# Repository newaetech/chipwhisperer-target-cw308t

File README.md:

# ChipWhisperer CW308 Targets #

These are *targets* for the CW308 UFO Board. This repo contains gerbers, schematics, and source files (in Altium Designer format). Note **SOME BOARDS ARE UNTESTED**. All files are provided at your own risk. The CW308 UFO board is required for use (not part of this repo) as it supplies power, clock, programming headers etc:

Many of these target boards (along with UFO baseboard) can be purchased assembled via Mouser Electronics. Note all targets are available however, so if you want some of the latest targets you may need to build one.

Most (all?) of these boards support the ChipWhisperer example applications. That means a basic HAL is provided in [chipwhisperer/firmware/mcu/hal](https://github.com/newaetech/chipwhisperer/tree/develop/firmware/mcu/hal) . Some of the more unique boards do not build as part of that system due to complexity of porting (i.e., ESP32).

## Documentation ##

The documentation in each directory (the markdown README.md file) is mirrored to the ChipWhisperer [main documentation page](https://chipwhisperer.readthedocs.io).
Some of the links in the markdown files here appear broken; they are written to
work for building the documentation site at
https://github.com/newaetech/chipwhisperer/tree/develop/docs, where this
repository is pulled in as a submodule.

## Using Boards ##

To use the boards, you will require the following at minimum:

* CW308 UFO Baseboard
* Analysis/injection device: either (1) ChipWhisperer-Lite Capture or ChipWhisperer-Pro, or (2) oscilloscope.

If NOT using ChipWhisperer-Lite/Pro which have built-in power supply, serial comms, and clock generator:

* USB-Serial adapter (3.3V)
* Crystal on UFO board (included w/ UFO board)
* 2.1mm DC power jack and 5V power supply

For most boards you will also require:
* External programming tool.

The STM32Fx boards, XMEGA, and AVR boards can all be programmed from the ChipWhisperer platform. All other boards will require an external programmer at this time.

### Suggested programmers ###

* For ARM targets anything with 20-pin JTAG header such as J-Link, OpenOCD, etc.
* For PowerPC targets a PEMicro USB Multilink
* For Tri-Core targets DAP miniWiggler V3
* For ESP32 you only need a USB-Serial cable
* Others (Si4010, D2000, etc) may have unique requirements.

## FAQs ##

**Q**: Do these boards work stand-alone?

**A**: No. These boards require a CW308 UFO Base-Board. In addition you may need an external programmer to load code on many of them.

--

**Q**: What's the difference between these and dev-boards?

**A**: These boards are purpose-built for side-channel analysis. As such they have a shunt resistor mounted, along with missing decoupling capacitors to allow clean power measurements. You can hack up dev-boards to achieve this, but these CW308T boards make it considerably easier to do so, along with high repeatability.

--

**Q:** Why are these boards so expensive when there is nothing on it? I can buy a dev-kit with JTAG and everything for the cost of some of these boards!

**A:** Dev-boards have low cost as are produced in huge quantity and minimal profit margin. Due to the unique nature of our boards we typically are producing QTY 25-200 per "run", and many of the ICs alone are rather expensive at that point. For example a STM32F407 @ Qty 40 is $12 USD, and the "discovery" board with that chip mounted is only $20!

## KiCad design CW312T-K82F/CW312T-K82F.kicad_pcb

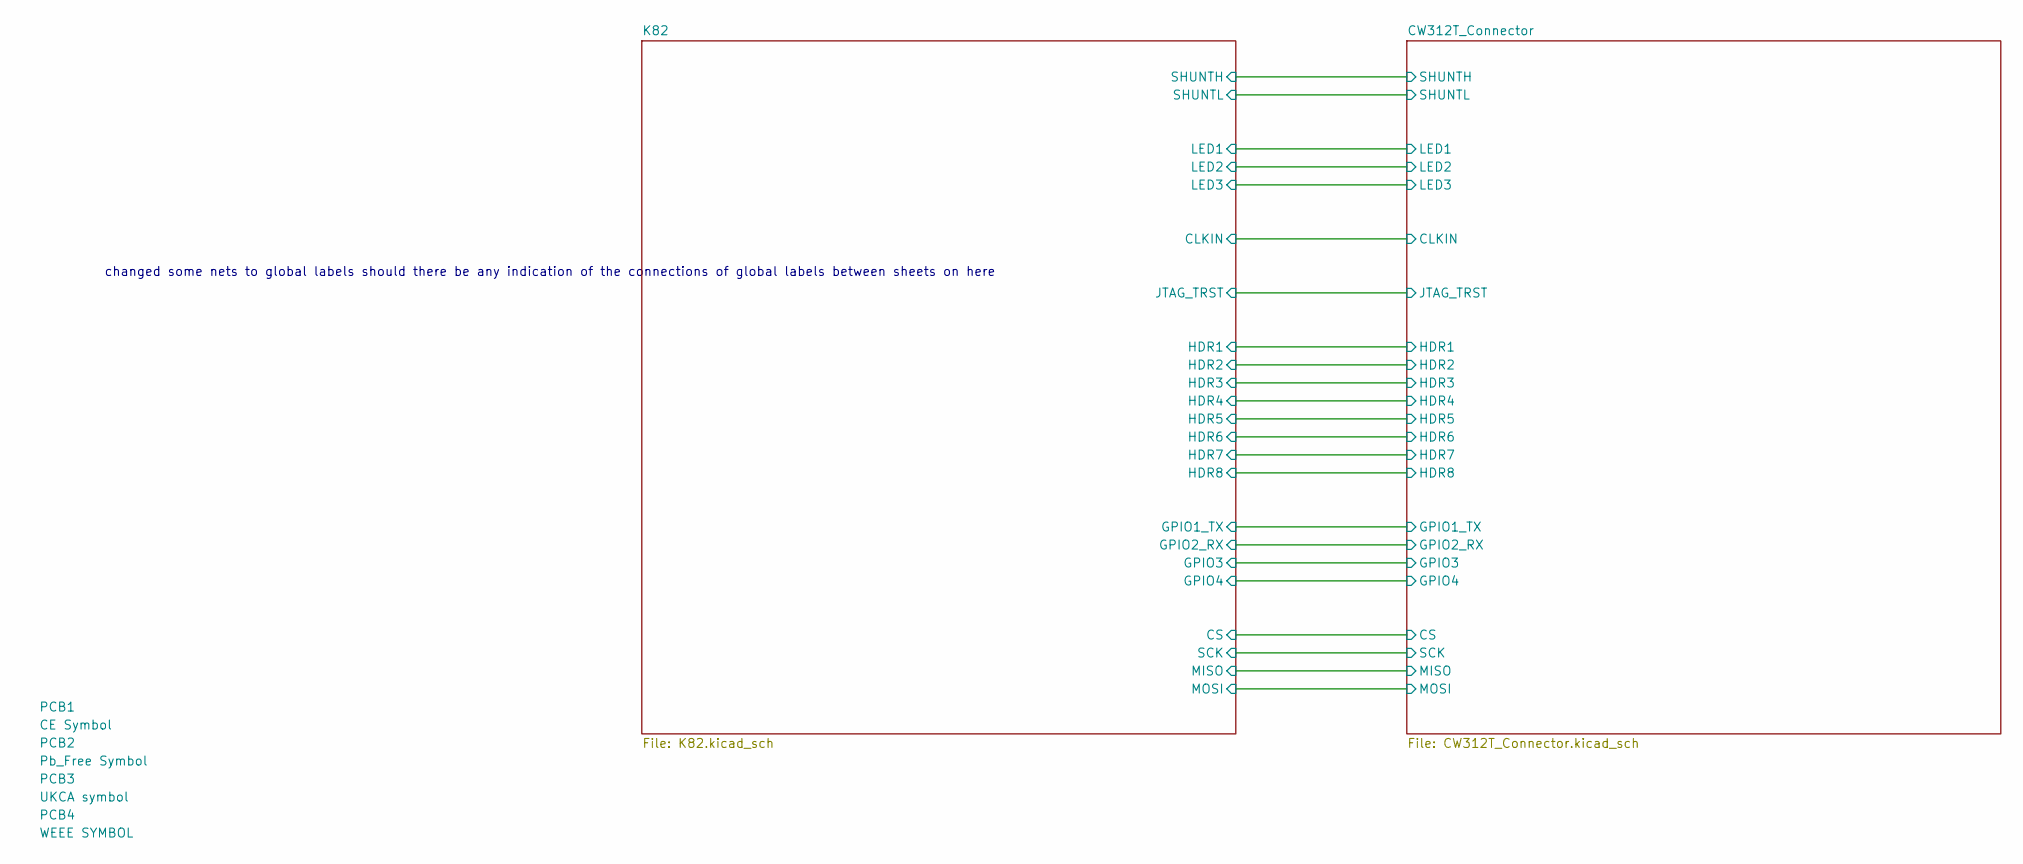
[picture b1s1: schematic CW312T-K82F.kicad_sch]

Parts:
PCB1: CE Symbol; CE-Logo_8.5x6mm_SilkScreen
PCB2: Pb_Free Symbol; Pb_Free_8.0x8.0mm_SilkScreen
PCB3: UKCA symbol; UKCA-Logo_8x8mm_SilkScreen
PCB4: WEEE SYMBOL; WEEE-Logo_5.6x8mm_SilkScreen

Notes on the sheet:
changed some nets to global labels should there be any indication of the connections of global labels between sheets on here

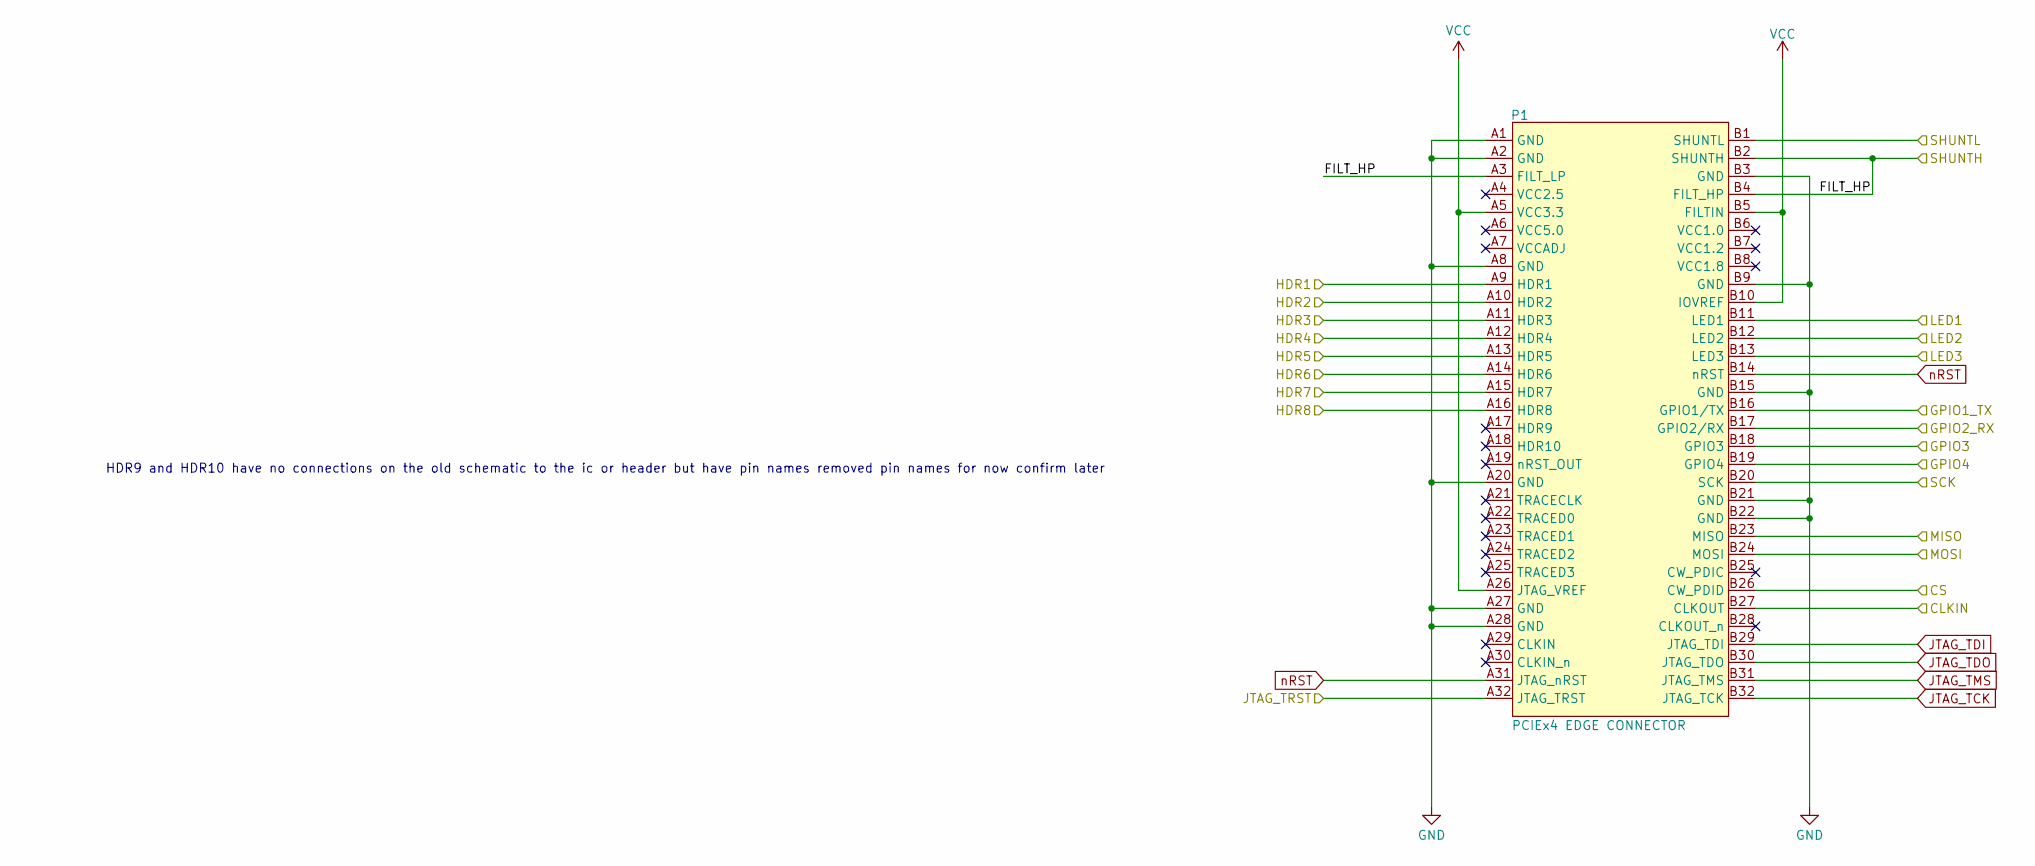
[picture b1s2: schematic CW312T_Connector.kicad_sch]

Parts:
P1: PCIEx4 EDGE CONNECTOR; CW312_Template

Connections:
/CW312T_Connector/CLKIN: P1.B27 (CLKOUT); also elsewhere on the board
/CW312T_Connector/CS: P1.B26 (CW_PDID); also elsewhere on the board
/CW312T_Connector/FILT_HP: P1.A3 (FILT_LP), P1.B2 (SHUNTH), P1.B4 (FILT_HP); also elsewhere on the board
/CW312T_Connector/GPIO1_TX: P1.B16 (GPIO1/TX); also elsewhere on the board
/CW312T_Connector/GPIO2_RX: P1.B17 (GPIO2/RX); also elsewhere on the board
/CW312T_Connector/GPIO3: P1.B18 (GPIO3); also elsewhere on the board
/CW312T_Connector/GPIO4: P1.B19 (GPIO4); also elsewhere on the board
/CW312T_Connector/HDR1: P1.A9 (HDR1); also elsewhere on the board
/CW312T_Connector/HDR2: P1.A10 (HDR2); also elsewhere on the board
/CW312T_Connector/HDR3: P1.A11 (HDR3); also elsewhere on the board
/CW312T_Connector/HDR4: P1.A12 (HDR4); also elsewhere on the board
/CW312T_Connector/HDR5: P1.A13 (HDR5); also elsewhere on the board
/CW312T_Connector/HDR6: P1.A14 (HDR6); also elsewhere on the board
/CW312T_Connector/HDR7: P1.A15 (HDR7); also elsewhere on the board
/CW312T_Connector/HDR8: P1.A16 (HDR8); also elsewhere on the board
/CW312T_Connector/JTAG_TRST: P1.A32 (JTAG_TRST); also elsewhere on the board
/CW312T_Connector/LED1: P1.B11 (LED1); also elsewhere on the board
/CW312T_Connector/LED2: P1.B12 (LED2); also elsewhere on the board
/CW312T_Connector/LED3: P1.B13 (LED3); also elsewhere on the board
/CW312T_Connector/MISO: P1.B23 (MISO); also elsewhere on the board
/CW312T_Connector/MOSI: P1.B24 (MOSI); also elsewhere on the board
/CW312T_Connector/SCK: P1.B20 (SCK); also elsewhere on the board
/CW312T_Connector/SHUNTL: P1.B1 (SHUNTL); also elsewhere on the board
GND: P1.A1 (GND), P1.A2 (GND), P1.A8 (GND), P1.A20 (GND), P1.A27 (GND), P1.A28 (GND), P1.B3 (GND), P1.B9 (GND), P1.B15 (GND), P1.B21 (GND), P1.B22 (GND); also elsewhere on the board
JTAG_TCK: P1.B32 (JTAG_TCK); also elsewhere on the board
JTAG_TDI: P1.B29 (JTAG_TDI); also elsewhere on the board
JTAG_TDO: P1.B30 (JTAG_TDO); also elsewhere on the board
JTAG_TMS: P1.B31 (JTAG_TMS); also elsewhere on the board
VCC: P1.A5 (VCC3.3), P1.A26 (JTAG_VREF), P1.B5 (FILTIN), P1.B10 (IOVREF); also elsewhere on the board
nRST: P1.A31 (JTAG_nRST), P1.B14 (nRST); also elsewhere on the board

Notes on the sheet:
HDR9 and HDR10 have no connections on the old schematic to the ic or header but have pin names removed pin names for now confirm later

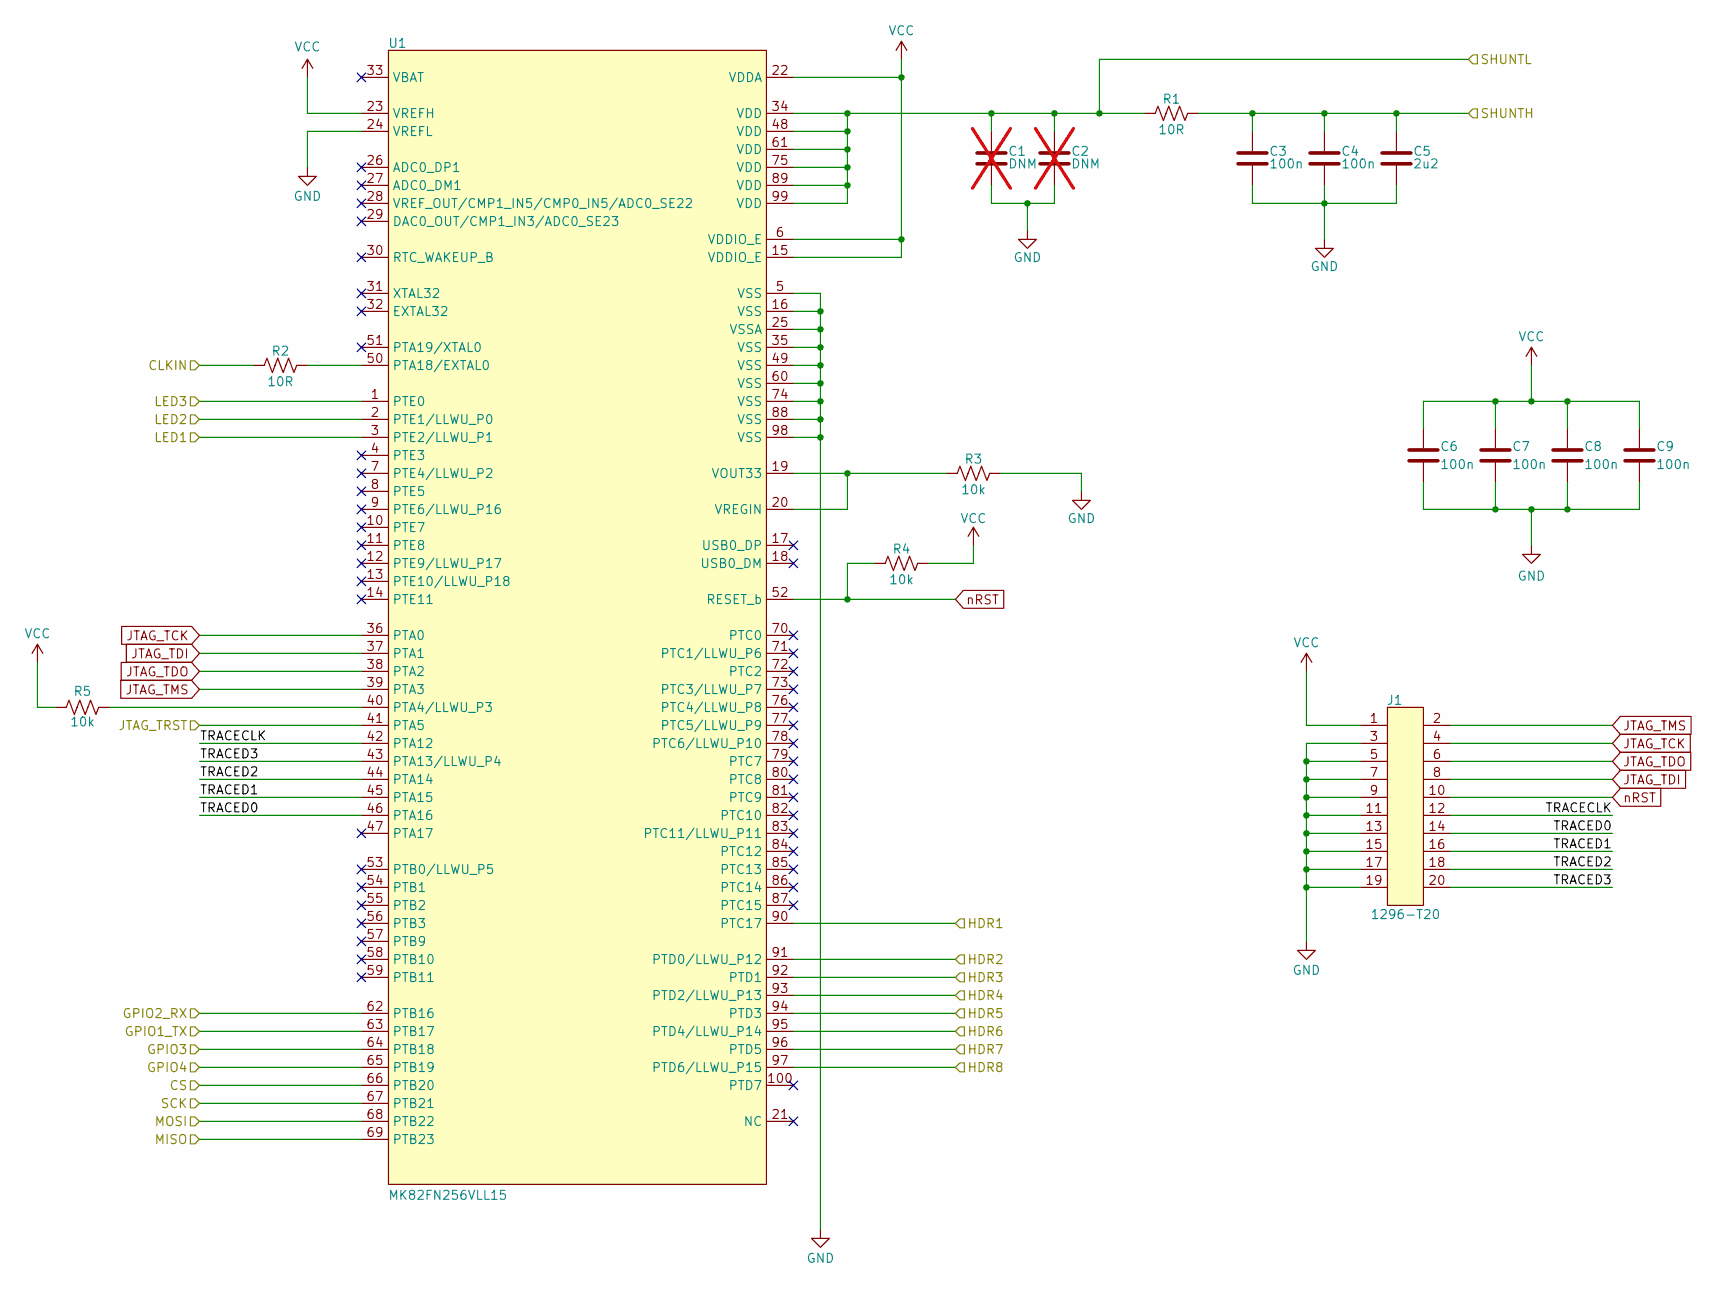
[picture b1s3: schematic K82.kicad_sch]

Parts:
C1, C2: DNM_CAP_0603; C_0603_1608Metric; Manufacturer Part Number C0603C225K4PAC7867; not fitted
C3, C4, C6, C7, C8, C9: CAP_100n_6.3V_0603; C_0603_1608Metric; Manufacturer Part Number CC0603KRX7R5BB104
C5: CAP_2u2_6.3V_0603; C_0603_1608Metric; Manufacturer Part Number CC0603KRX7R5BB225
J1: 20_pin; PinHeader_2x10_P1.27mm_Vertical_SMD; Manufacturer Part Number 20021121-00020T4LF
R1, R2: RES_10R_0603; R_0603_1608Metric; Manufacturer Part Number RC0603FR-0710RL
R3, R4, R5: RES_10k_0603; R_0603_1608Metric; Manufacturer Part Number RC0603FR-0710KL
U1: MK82FN256VLL15; LQFP-100_14x14mm_P0.5mm; Manufacturer Part Number MK82FN256VLL15

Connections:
/CW312T_Connector/CLKIN: R2.1; also elsewhere on the board
/CW312T_Connector/CS: U1.66 (PTB20); also elsewhere on the board
/CW312T_Connector/FILT_HP: C3.2, C4.2, C5.2, R1.2; also elsewhere on the board
/CW312T_Connector/GPIO1_TX: U1.63 (PTB17); also elsewhere on the board
/CW312T_Connector/GPIO2_RX: U1.62 (PTB16); also elsewhere on the board
/CW312T_Connector/GPIO3: U1.64 (PTB18); also elsewhere on the board
/CW312T_Connector/GPIO4: U1.65 (PTB19); also elsewhere on the board
/CW312T_Connector/HDR1: U1.90 (PTC17); also elsewhere on the board
/CW312T_Connector/HDR2: U1.91 (PTD0/LLWU_P12); also elsewhere on the board
/CW312T_Connector/HDR3: U1.92 (PTD1); also elsewhere on the board
/CW312T_Connector/HDR4: U1.93 (PTD2/LLWU_P13); also elsewhere on the board
/CW312T_Connector/HDR5: U1.94 (PTD3); also elsewhere on the board
/CW312T_Connector/HDR6: U1.95 (PTD4/LLWU_P14); also elsewhere on the board
/CW312T_Connector/HDR7: U1.96 (PTD5); also elsewhere on the board
/CW312T_Connector/HDR8: U1.97 (PTD6/LLWU_P15); also elsewhere on the board
/CW312T_Connector/JTAG_TRST: U1.41 (PTA5); also elsewhere on the board
/CW312T_Connector/LED1: U1.3 (PTE2/LLWU_P1); also elsewhere on the board
/CW312T_Connector/LED2: U1.2 (PTE1/LLWU_P0); also elsewhere on the board
/CW312T_Connector/LED3: U1.1 (PTE0); also elsewhere on the board
/CW312T_Connector/MISO: U1.69 (PTB23); also elsewhere on the board
/CW312T_Connector/MOSI: U1.68 (PTB22); also elsewhere on the board
/CW312T_Connector/SCK: U1.67 (PTB21); also elsewhere on the board
/CW312T_Connector/SHUNTL: C1.2, C2.2, R1.1, U1.34 (VDD), U1.48 (VDD), U1.61 (VDD), U1.75 (VDD), U1.89 (VDD), U1.99 (VDD); also elsewhere on the board
/K82/TRACECLK: J1.12, U1.42 (PTA12)
/K82/TRACED0: J1.14, U1.46 (PTA16)
/K82/TRACED1: J1.16, U1.45 (PTA15)
/K82/TRACED2: J1.18, U1.44 (PTA14)
/K82/TRACED3: J1.20, U1.43 (PTA13/LLWU_P4)
GND: C1.1, C2.1, C3.1, C4.1, C5.1, C6.1, C7.1, C8.1, C9.1, J1.3, J1.5, J1.7, J1.9, J1.11, J1.13, J1.15, J1.17, J1.19, R3.2, U1.5 (VSS), U1.16 (VSS), U1.24 (VREFL), U1.25 (VSSA), U1.35 (VSS), U1.49 (VSS), U1.60 (VSS), U1.74 (VSS), U1.88 (VSS), U1.98 (VSS); also elsewhere on the board
JTAG_TCK: J1.4, U1.36 (PTA0); also elsewhere on the board
JTAG_TDI: J1.8, U1.37 (PTA1); also elsewhere on the board
JTAG_TDO: J1.6, U1.38 (PTA2); also elsewhere on the board
JTAG_TMS: J1.2, U1.39 (PTA3); also elsewhere on the board
unnamed: R5.2, U1.40 (PTA4/LLWU_P3)
unnamed: R2.2, U1.50 (PTA18/EXTAL0)
unnamed: R3.1, U1.19 (VOUT33), U1.20 (VREGIN)
VCC: C6.2, C7.2, C8.2, C9.2, J1.1, R4.2, R5.1, U1.6 (VDDIO_E), U1.15 (VDDIO_E), U1.22 (VDDA), U1.23 (VREFH); also elsewhere on the board
nRST: J1.10, R4.1, U1.52 (RESET_b); also elsewhere on the board

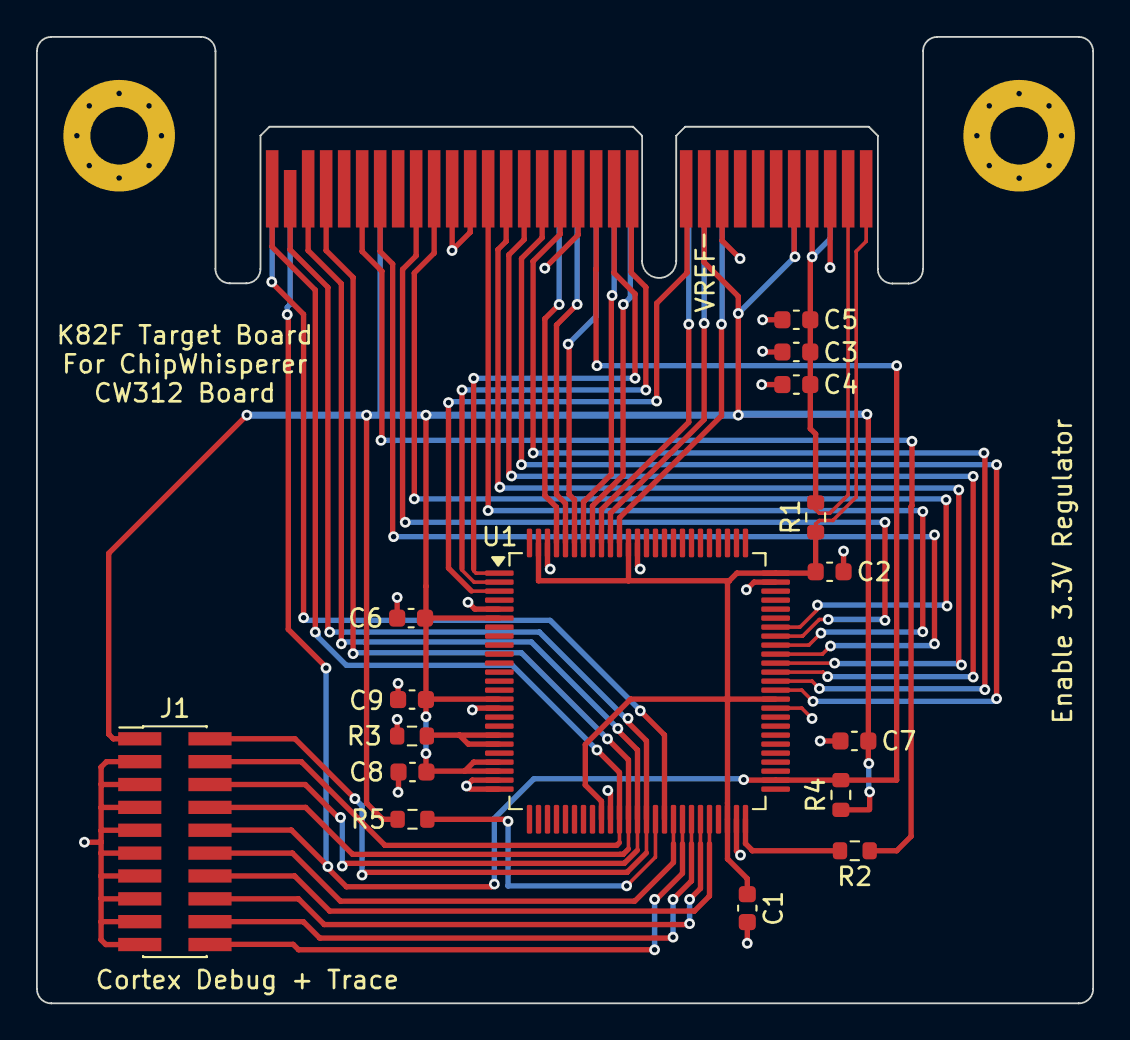
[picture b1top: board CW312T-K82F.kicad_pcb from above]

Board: 2 copper layers, 58.7 x 53.7 mm, 21 parts (0 on the bottom side), 38 nets.

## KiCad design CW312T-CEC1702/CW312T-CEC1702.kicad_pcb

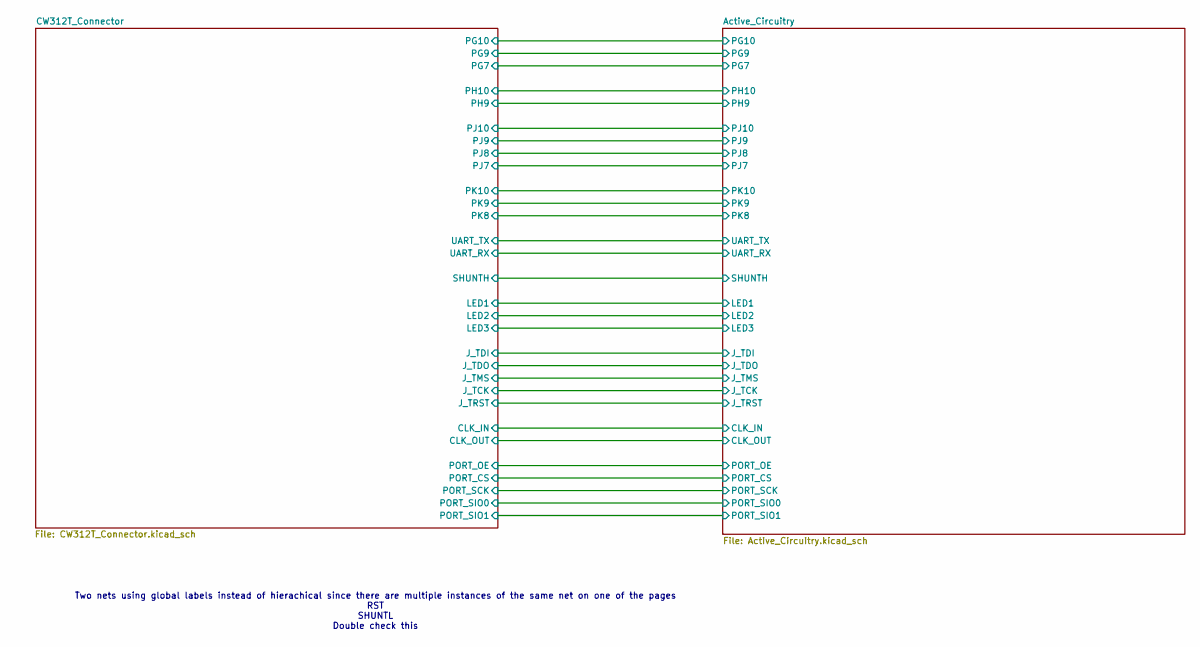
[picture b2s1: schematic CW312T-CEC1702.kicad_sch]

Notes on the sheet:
Two nets using global labels instead of hierachical since there are multiple instances of the same net on one of the pages RST SHUNTL Double check this

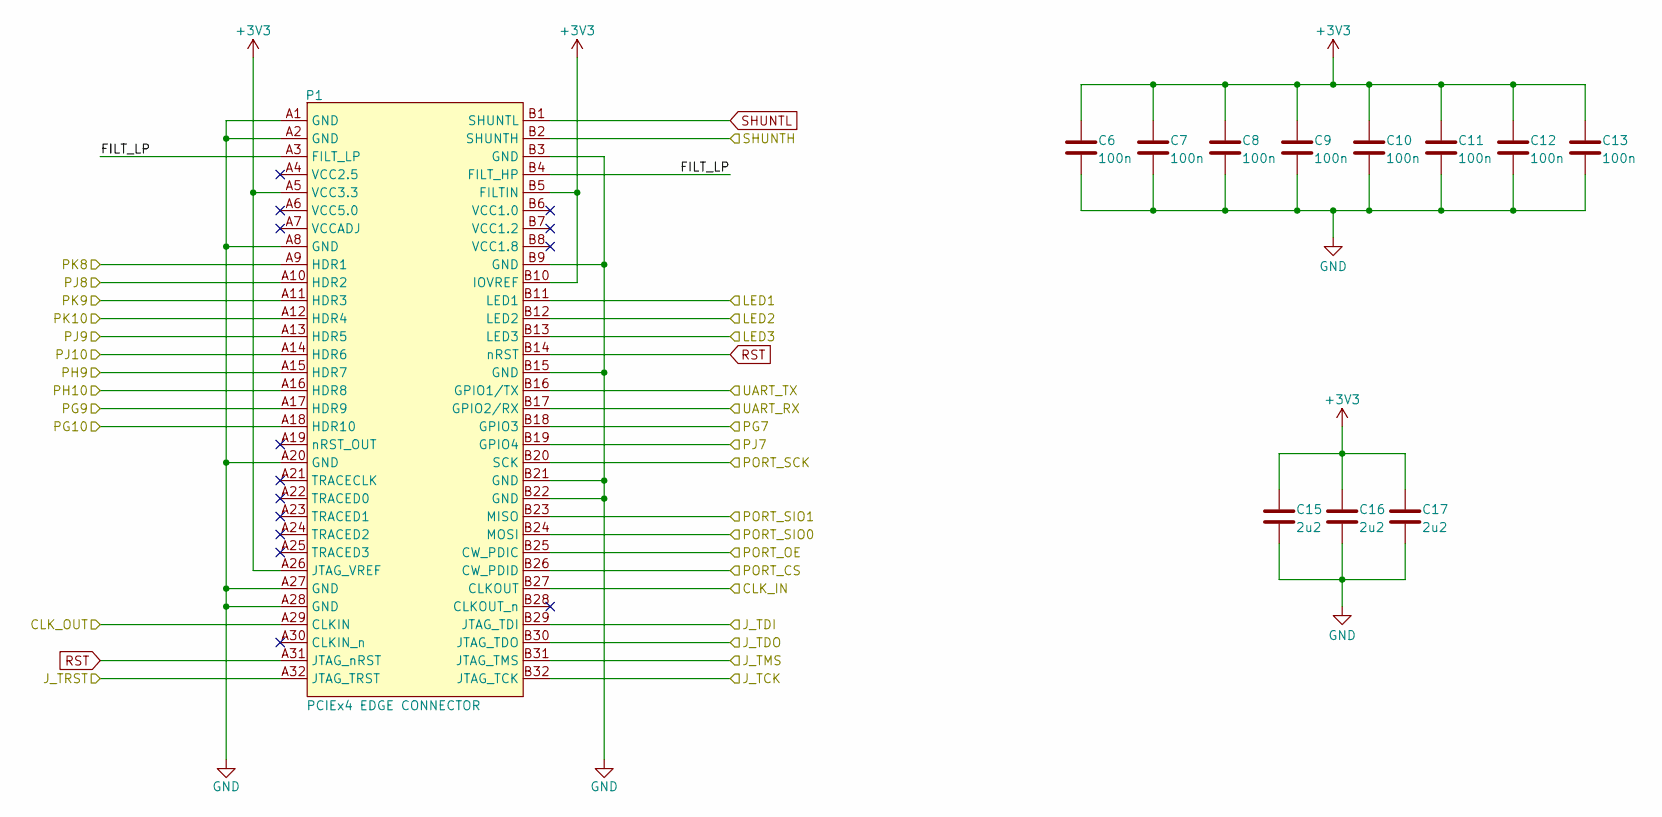
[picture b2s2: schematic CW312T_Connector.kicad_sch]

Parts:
C6, C7, C8, C9, C10, C11, C12, C13: CAP_100n_6.3V_0603; C_0603_1608Metric; Manufacturer Part Number CC0603KRX7R5BB104
C15, C16, C17: CAP_2u2_6.3V_0603; C_0603_1608Metric; Manufacturer Part Number CC0603KRX7R5BB225
P1: PCIEx4 EDGE CONNECTOR; CW312_Template

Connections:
+3V3: C6.2, C7.2, C8.2, C9.2, C10.2, C11.2, C12.2, C13.2, C15.2, C16.2, C17.2, P1.A5 (VCC3.3), P1.A26 (JTAG_VREF), P1.B5 (FILTIN), P1.B10 (IOVREF); also elsewhere on the board
/Active_Circuitry/CLK_IN: P1.B27 (CLKOUT); also elsewhere on the board
/Active_Circuitry/CLK_OUT: P1.A29 (CLKIN); also elsewhere on the board
/Active_Circuitry/J_TCK: P1.B32 (JTAG_TCK); also elsewhere on the board
/Active_Circuitry/J_TDI: P1.B29 (JTAG_TDI); also elsewhere on the board
/Active_Circuitry/J_TDO: P1.B30 (JTAG_TDO); also elsewhere on the board
/Active_Circuitry/J_TMS: P1.B31 (JTAG_TMS); also elsewhere on the board
/Active_Circuitry/J_TRST: P1.A32 (JTAG_TRST); also elsewhere on the board
/Active_Circuitry/LED1: P1.B11 (LED1); also elsewhere on the board
/Active_Circuitry/LED2: P1.B12 (LED2); also elsewhere on the board
/Active_Circuitry/LED3: P1.B13 (LED3); also elsewhere on the board
/Active_Circuitry/PG7: P1.B18 (GPIO3); also elsewhere on the board
/Active_Circuitry/PG9: P1.A17 (HDR9); also elsewhere on the board
/Active_Circuitry/PG10: P1.A18 (HDR10); also elsewhere on the board
/Active_Circuitry/PH9: P1.A15 (HDR7); also elsewhere on the board
/Active_Circuitry/PH10: P1.A16 (HDR8); also elsewhere on the board
/Active_Circuitry/PJ7: P1.B19 (GPIO4); also elsewhere on the board
/Active_Circuitry/PJ8: P1.A10 (HDR2); also elsewhere on the board
/Active_Circuitry/PJ9: P1.A13 (HDR5); also elsewhere on the board
/Active_Circuitry/PJ10: P1.A14 (HDR6); also elsewhere on the board
/Active_Circuitry/PK8: P1.A9 (HDR1); also elsewhere on the board
/Active_Circuitry/PK9: P1.A11 (HDR3); also elsewhere on the board
/Active_Circuitry/PK10: P1.A12 (HDR4); also elsewhere on the board
/Active_Circuitry/PORT_CS: P1.B26 (CW_PDID); also elsewhere on the board
/Active_Circuitry/PORT_OE: P1.B25 (CW_PDIC); also elsewhere on the board
/Active_Circuitry/PORT_SCK: P1.B20 (SCK); also elsewhere on the board
/Active_Circuitry/PORT_SIO0: P1.B24 (MOSI); also elsewhere on the board
/Active_Circuitry/PORT_SIO1: P1.B23 (MISO); also elsewhere on the board
/Active_Circuitry/SHUNTH: P1.B2 (SHUNTH); also elsewhere on the board
/Active_Circuitry/UART_RX: P1.B17 (GPIO2/RX); also elsewhere on the board
/Active_Circuitry/UART_TX: P1.B16 (GPIO1/TX); also elsewhere on the board
/CW312T_Connector/FILT_LP: P1.A3 (FILT_LP), P1.B4 (FILT_HP)
GND: C6.1, C7.1, C8.1, C9.1, C10.1, C11.1, C12.1, C13.1, C15.1, C16.1, C17.1, P1.A1 (GND), P1.A2 (GND), P1.A8 (GND), P1.A20 (GND), P1.A27 (GND), P1.A28 (GND), P1.B3 (GND), P1.B9 (GND), P1.B15 (GND), P1.B21 (GND), P1.B22 (GND); also elsewhere on the board
RST: P1.A31 (JTAG_nRST), P1.B14 (nRST); also elsewhere on the board
SHUNTL: P1.B1 (SHUNTL); also elsewhere on the board

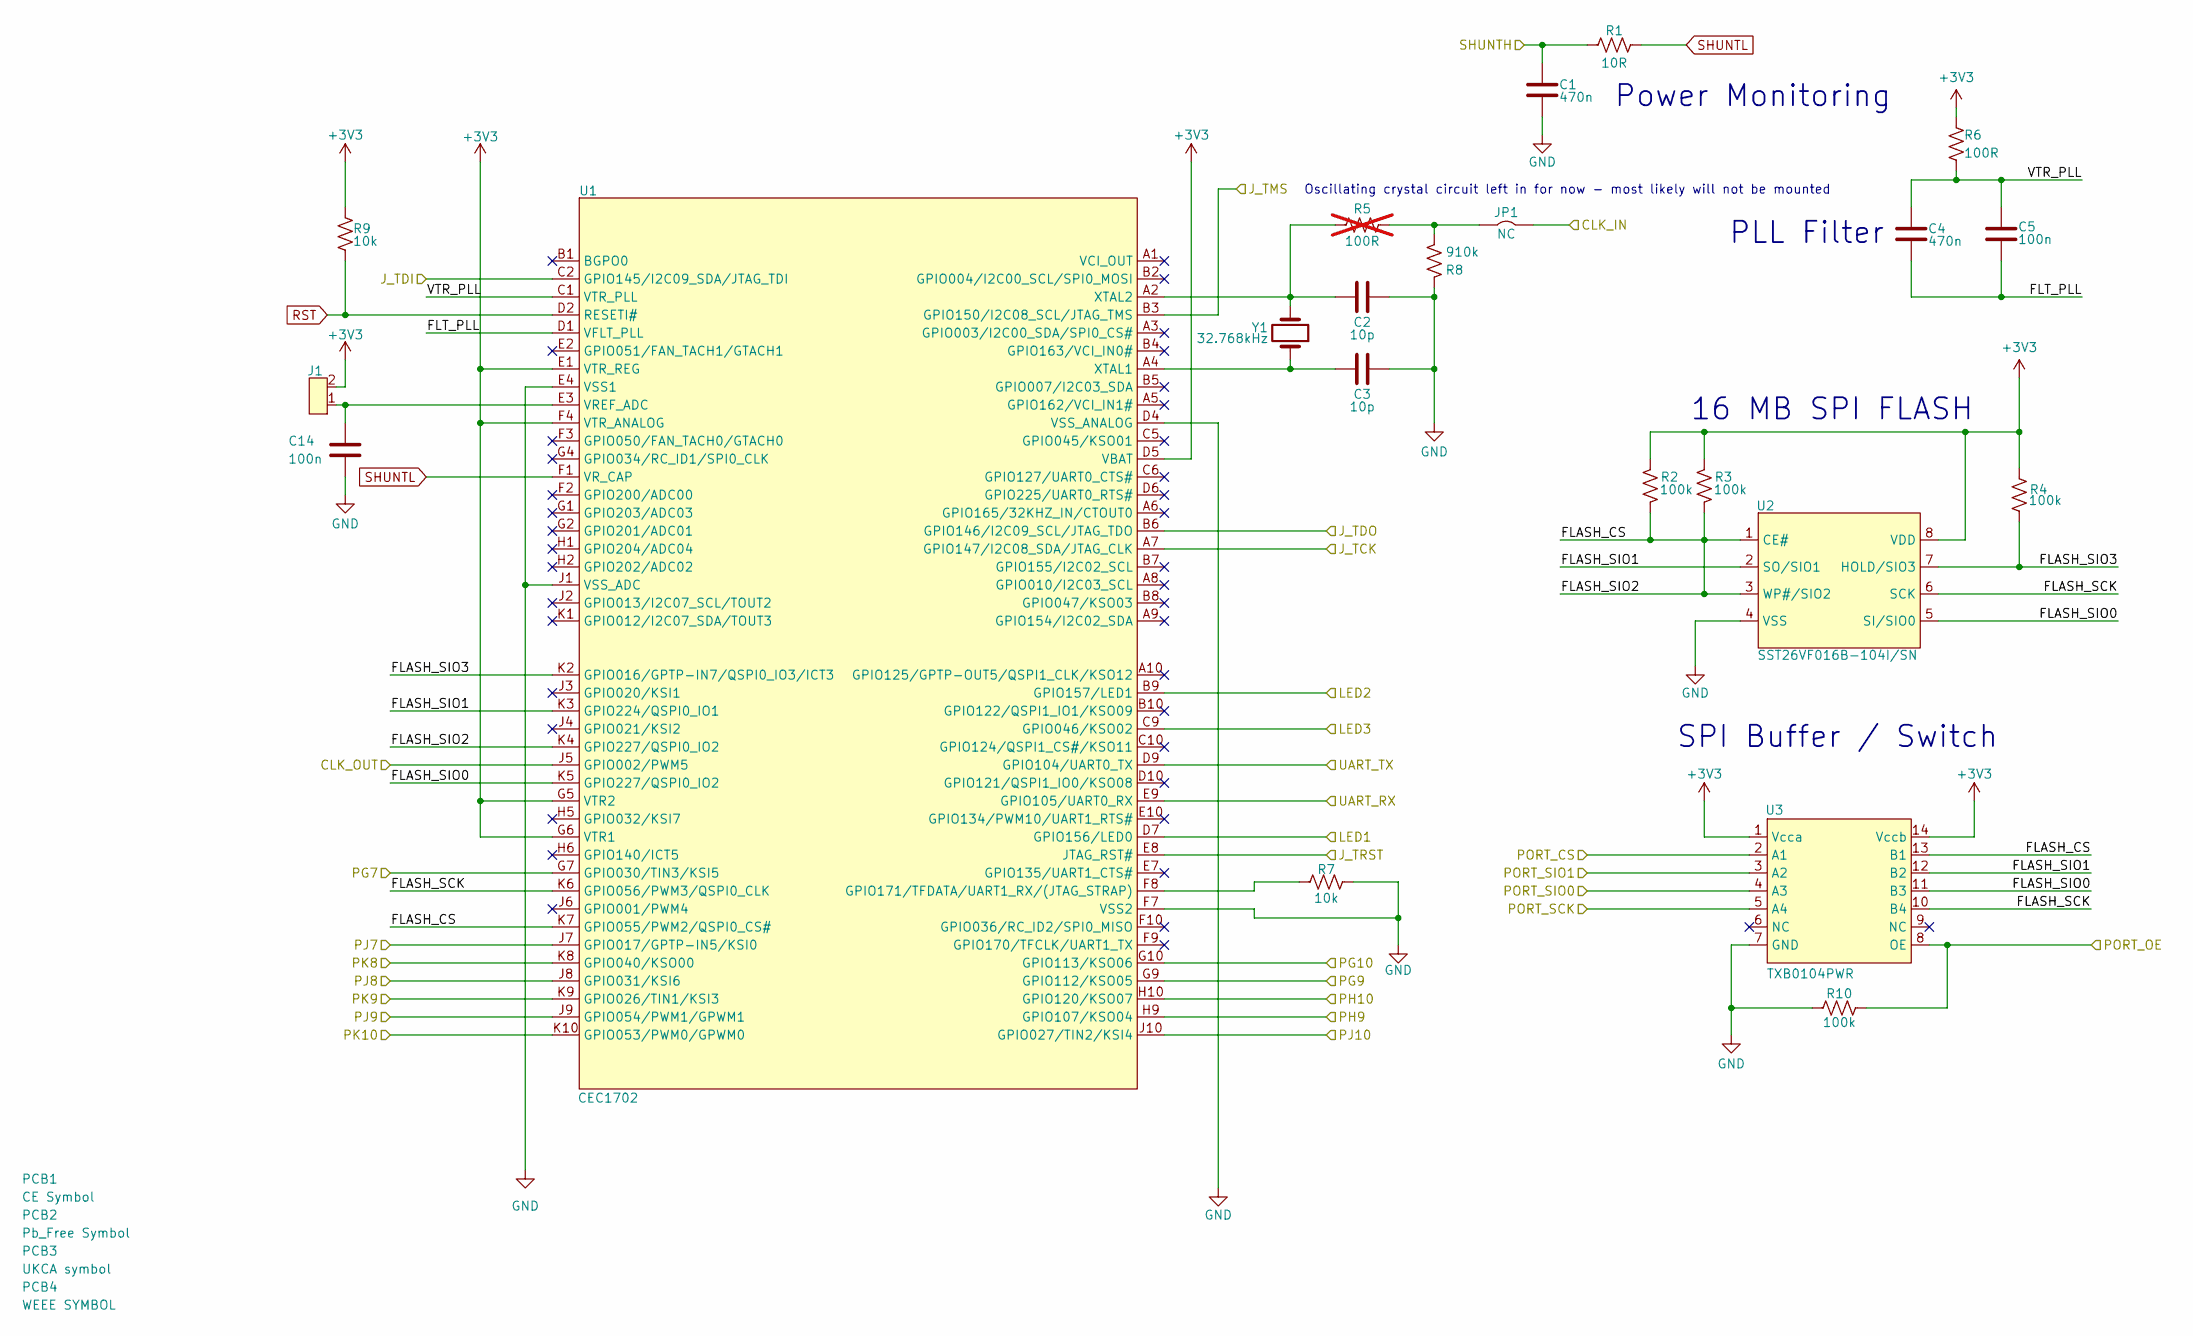
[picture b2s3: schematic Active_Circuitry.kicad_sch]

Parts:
C1, C4: CAP_470n_10V_0603; C_0603_1608Metric; Manufacturer Part Number CC0603KRX7R6BB474
C2, C3: CAP_10p_50V_0603; C_0603_1608Metric; Manufacturer Part Number CC0603JRNPO9BN100
C5: CAP_100n_6.3V_0603; C_0603_1608Metric; Manufacturer Part Number CC0603KRX7R5BB104
C14: CAP_100n_50V_0603; C_0603_1608Metric; Manufacturer Part Number CC0603KRX7R9BB104
J1: 2Pin_Header_2.54; PinHeader_2x01_P2.54mm_Vertical; Manufacturer Part Number M20-9990246
JP1: SolderJumper-2_P1.3mm_Bridged2Bar_Pad1.0x1.5mm
PCB1: CE Symbol; CE-Logo_8.5x6mm_SilkScreen
PCB2: Pb_Free Symbol; Pb_Free_8.0x8.0mm_SilkScreen
PCB3: UKCA symbol; UKCA-Logo_8x8mm_SilkScreen
PCB4: WEEE SYMBOL; WEEE-Logo_5.6x8mm_SilkScreen
R1: RES_10R_0603; R_0603_1608Metric; Manufacturer Part Number RC0603FR-0710RL
R2, R3, R4, R10: RES_100k_0603; R_0603_1608Metric; Manufacturer Part Number RC0603FR-07100KL
R5: RES_100R_0603; R_0603_1608Metric; Manufacturer Part Number RC0603FR-07100RL; not fitted
R6: RES_100R_0603; R_0603_1608Metric; Manufacturer Part Number RC0603FR-07100RL
R7, R9: RES_10k_0603; R_0603_1608Metric; Manufacturer Part Number RC0603FR-0710KL
R8: RES_910k_0603; R_0603_1608Metric; Manufacturer Part Number RC0603FR-07910KL
U1: CEC1702; BGA84C65P10X10_700X700X80; Manufacturer Part Number CEC1702Q-B1-SX-TR
U2: SST26VF016B-104I/SN; SOIC-8_3.9x4.9mm_P1.27mm; Manufacturer Part Number SST26VF016B-104I/SN
U3: TXB0104PWR; SOIC-14_3.9x8.7mm_P1.27mm; Manufacturer Part Number TXB0104PWR
Y1: 32.768kHz; Crystal_SMD_3215-2Pin_3.2x1.5mm; Manufacturer Part Number FC-135 32.7680KA-K0

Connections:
+3V3: J1.2, R2.2, R3.2, R4.1, R6.2, R9.2, U1.D5 (VBAT), U1.E1 (VTR_REG), U1.F4 (VTR_ANALOG), U1.G5 (VTR2), U1.G6 (VTR1), U2.8 (VDD), U3.1 (Vcca), U3.14 (Vccb); also elsewhere on the board
/Active_Circuitry/CLK_IN: JP1.1; also elsewhere on the board
/Active_Circuitry/CLK_OUT: U1.J5 (GPIO002/PWM5); also elsewhere on the board
/Active_Circuitry/FLASH_CS: R2.1, R3.1, U1.K4 (GPIO227/QSPI0_IO2), U1.K7 (GPIO055/PWM2/QSPI0_CS#), U2.1 (CE#), U2.3 (WP#/SIO2), U3.13 (B1)
/Active_Circuitry/FLASH_SCK: U1.K6 (GPIO056/PWM3/QSPI0_CLK), U2.6 (SCK), U3.10 (B4)
/Active_Circuitry/FLASH_SIO0: U1.K5 (GPIO227/QSPI0_IO2), U2.5 (SI/SIO0), U3.11 (B3)
/Active_Circuitry/FLASH_SIO1: U1.K3 (GPIO224/QSPI0_IO1), U2.2 (SO/SIO1), U3.12 (B2)
/Active_Circuitry/FLASH_SIO3: R4.2, U1.K2 (GPIO016/GPTP-IN7/QSPI0_IO3/ICT3), U2.7 (HOLD/SIO3)
/Active_Circuitry/FLT_PLL: C4.1, C5.1, U1.D1 (VFLT_PLL)
/Active_Circuitry/J_TCK: U1.A7 (GPIO147/I2C08_SDA/JTAG_CLK); also elsewhere on the board
/Active_Circuitry/J_TDI: U1.C2 (GPIO145/I2C09_SDA/JTAG_TDI); also elsewhere on the board
/Active_Circuitry/J_TDO: U1.B6 (GPIO146/I2C09_SCL/JTAG_TDO); also elsewhere on the board
/Active_Circuitry/J_TMS: U1.B3 (GPIO150/I2C08_SCL/JTAG_TMS); also elsewhere on the board
/Active_Circuitry/J_TRST: U1.E8 (JTAG_RST#); also elsewhere on the board
/Active_Circuitry/LED1: U1.D7 (GPIO156/LED0); also elsewhere on the board
/Active_Circuitry/LED2: U1.B9 (GPIO157/LED1); also elsewhere on the board
/Active_Circuitry/LED3: U1.C9 (GPIO046/KSO02); also elsewhere on the board
/Active_Circuitry/PG7: U1.G7 (GPIO030/TIN3/KSI5); also elsewhere on the board
/Active_Circuitry/PG9: U1.G9 (GPIO112/KSO05); also elsewhere on the board
/Active_Circuitry/PG10: U1.G10 (GPIO113/KSO06); also elsewhere on the board
/Active_Circuitry/PH9: U1.H9 (GPIO107/KSO04); also elsewhere on the board
/Active_Circuitry/PH10: U1.H10 (GPIO120/KSO07); also elsewhere on the board
/Active_Circuitry/PJ7: U1.J7 (GPIO017/GPTP-IN5/KSI0); also elsewhere on the board
/Active_Circuitry/PJ8: U1.J8 (GPIO031/KSI6); also elsewhere on the board
/Active_Circuitry/PJ9: U1.J9 (GPIO054/PWM1/GPWM1); also elsewhere on the board
/Active_Circuitry/PJ10: U1.J10 (GPIO027/TIN2/KSI4); also elsewhere on the board
/Active_Circuitry/PK8: U1.K8 (GPIO040/KSO00); also elsewhere on the board
/Active_Circuitry/PK9: U1.K9 (GPIO026/TIN1/KSI3); also elsewhere on the board
/Active_Circuitry/PK10: U1.K10 (GPIO053/PWM0/GPWM0); also elsewhere on the board
/Active_Circuitry/PORT_CS: U3.2 (A1); also elsewhere on the board
/Active_Circuitry/PORT_OE: R10.2, U3.8 (OE); also elsewhere on the board
/Active_Circuitry/PORT_SCK: U3.5 (A4); also elsewhere on the board
/Active_Circuitry/PORT_SIO0: U3.4 (A3); also elsewhere on the board
/Active_Circuitry/PORT_SIO1: U3.3 (A2); also elsewhere on the board
/Active_Circuitry/SHUNTH: C1.2, R1.1; also elsewhere on the board
/Active_Circuitry/UART_RX: U1.E9 (GPIO105/UART0_RX); also elsewhere on the board
/Active_Circuitry/UART_TX: U1.D9 (GPIO104/UART0_TX); also elsewhere on the board
/Active_Circuitry/VTR_PLL: C4.2, C5.2, R6.1, U1.C1 (VTR_PLL)
GND: C1.1, C2.2, C3.2, C14.1, R7.2, R8.2, R10.1, U1.D4 (VSS_ANALOG), U1.E4 (VSS1), U1.F7 (VSS2), U1.J1 (VSS_ADC), U2.4 (VSS), U3.7 (GND); also elsewhere on the board
unnamed: JP1.2, R5.2, R8.1
unnamed: R7.1, U1.F8 (GPIO171/TFDATA/UART1_RX/(JTAG_STRAP))
unnamed: C14.2, J1.1, U1.E3 (VREF_ADC)
unnamed: C3.1, U1.A4 (XTAL1), Y1.1
unnamed: C2.1, R5.1, U1.A2 (XTAL2), Y1.2
RST: R9.1, U1.D2 (RESETI#); also elsewhere on the board
SHUNTL: R1.2, U1.F1 (VR_CAP); also elsewhere on the board

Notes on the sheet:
PLL Filter
16 MB SPI FLASH
Power Monitoring
Oscillating crystal circuit left in for now - most likely will not be mounted
SPI Buffer / Switch
